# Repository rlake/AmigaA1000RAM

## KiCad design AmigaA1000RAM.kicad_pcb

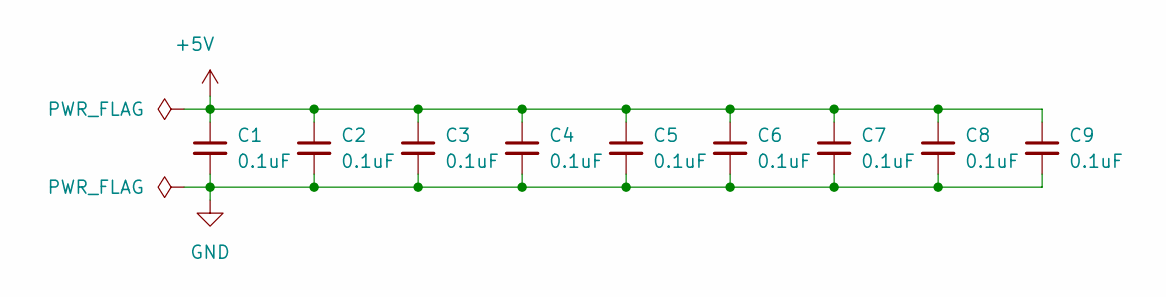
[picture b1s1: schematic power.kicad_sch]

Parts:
C1, C2, C3, C4, C5, C6, C7, C8, C9: 0.1uF; C_0805_2012Metric

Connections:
+5V: C1.1, C2.1, C3.1, C4.1, C5.1, C6.1, C7.1, C8.1, C9.1; also elsewhere on the board
GND: C1.2, C2.2, C3.2, C4.2, C5.2, C6.2, C7.2, C8.2, C9.2; also elsewhere on the board

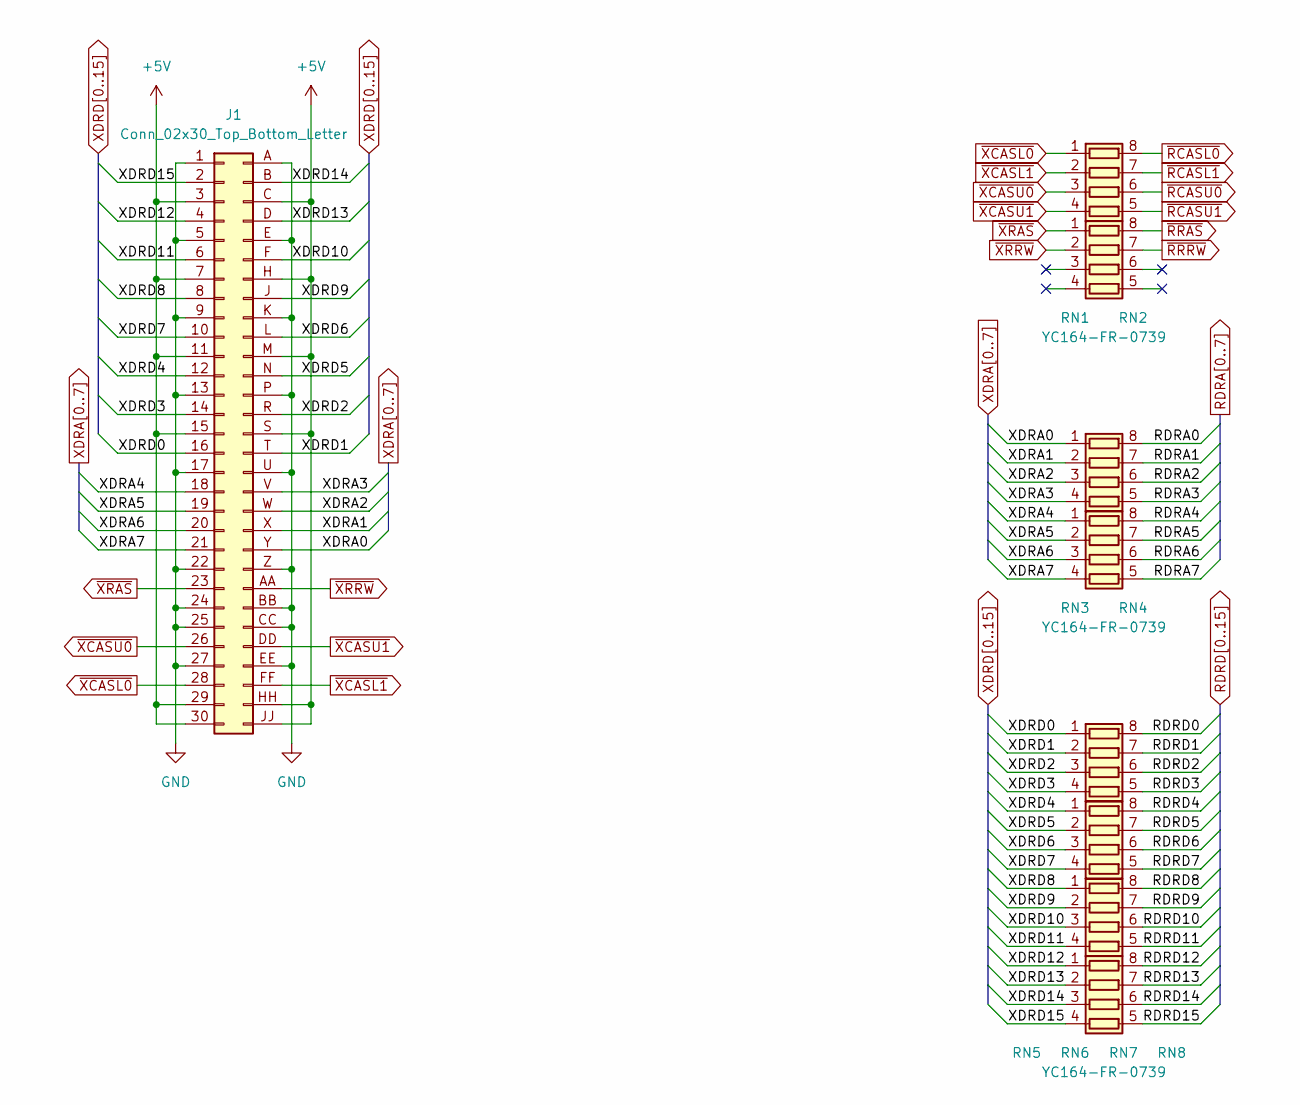
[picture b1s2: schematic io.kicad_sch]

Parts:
J1: Conn_02x30_Top_Bottom_Letter; CardEdgeSocket_2x30_P3.96mm
RN1, RN3, RN6, RN7, RN8: YC164-FR-0768; R_Array_Convex_4x0603
RN2, RN4, RN5: YC164-FR-0739; R_Array_Convex_4x0603

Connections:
+5V: J1.3, J1.7, J1.11, J1.15, J1.29, J1.30, J1.C, J1.H, J1.HH, J1.JJ, J1.M, J1.S; also elsewhere on the board
GND: J1.1, J1.5, J1.9, J1.13, J1.17, J1.22, J1.24, J1.25, J1.27, J1.A, J1.BB, J1.CC, J1.E, J1.EE, J1.K, J1.P, J1.U, J1.Z; also elsewhere on the board
RDRA0: RN3.8 (R1.2); also elsewhere on the board
RDRA1: RN3.7 (R2.2); also elsewhere on the board
RDRA2: RN3.6 (R3.2); also elsewhere on the board
RDRA3: RN3.5 (R4.2); also elsewhere on the board
RDRA4: RN4.8 (R1.2); also elsewhere on the board
RDRA5: RN4.7 (R2.2); also elsewhere on the board
RDRA6: RN4.6 (R3.2); also elsewhere on the board
RDRA7: RN4.5 (R4.2); also elsewhere on the board
RDRD0: RN5.8 (R1.2); also elsewhere on the board
RDRD1: RN5.7 (R2.2); also elsewhere on the board
RDRD2: RN5.6 (R3.2); also elsewhere on the board
RDRD3: RN5.5 (R4.2); also elsewhere on the board
RDRD4: RN6.8 (R1.2); also elsewhere on the board
RDRD5: RN6.7 (R2.2); also elsewhere on the board
RDRD6: RN6.6 (R3.2); also elsewhere on the board
RDRD7: RN6.5 (R4.2); also elsewhere on the board
RDRD8: RN7.8 (R1.2); also elsewhere on the board
RDRD9: RN7.7 (R2.2); also elsewhere on the board
RDRD10: RN7.6 (R3.2); also elsewhere on the board
RDRD11: RN7.5 (R4.2); also elsewhere on the board
RDRD12: RN8.8 (R1.2); also elsewhere on the board
RDRD13: RN8.7 (R2.2); also elsewhere on the board
RDRD14: RN8.6 (R3.2); also elsewhere on the board
RDRD15: RN8.5 (R4.2); also elsewhere on the board
XDRA0: J1.Y, RN3.1 (R1.1)
XDRA1: J1.X, RN3.2 (R2.1)
XDRA2: J1.W, RN3.3 (R3.1)
XDRA3: J1.V, RN3.4 (R4.1)
XDRA4: J1.18, RN4.1 (R1.1)
XDRA5: J1.19, RN4.2 (R2.1)
XDRA6: J1.20, RN4.3 (R3.1)
XDRA7: J1.21, RN4.4 (R4.1)
XDRD0: J1.16, RN5.1 (R1.1)
XDRD1: J1.T, RN5.2 (R2.1)
XDRD2: J1.R, RN5.3 (R3.1)
XDRD3: J1.14, RN5.4 (R4.1)
XDRD4: J1.12, RN6.1 (R1.1)
XDRD5: J1.N, RN6.2 (R2.1)
XDRD6: J1.L, RN6.3 (R3.1)
XDRD7: J1.10, RN6.4 (R4.1)
XDRD8: J1.8, RN7.1 (R1.1)
XDRD9: J1.J, RN7.2 (R2.1)
XDRD10: J1.F, RN7.3 (R3.1)
XDRD11: J1.6, RN7.4 (R4.1)
XDRD12: J1.4, RN8.1 (R1.1)
XDRD13: J1.D, RN8.2 (R2.1)
XDRD14: J1.B, RN8.3 (R3.1)
XDRD15: J1.2, RN8.4 (R4.1)
~RCASL0: RN1.8 (R1.2); also elsewhere on the board
~RCASL1: RN1.7 (R2.2); also elsewhere on the board
~RCASU0: RN1.6 (R3.2); also elsewhere on the board
~RCASU1: RN1.5 (R4.2); also elsewhere on the board
~RRAS: RN2.8 (R1.2); also elsewhere on the board
~RRRW: RN2.7 (R2.2); also elsewhere on the board
~XCASL0: J1.28, RN1.1 (R1.1)
~XCASL1: J1.FF, RN1.2 (R2.1)
~XCASU0: J1.26, RN1.3 (R3.1)
~XCASU1: J1.DD, RN1.4 (R4.1)
~XRAS: J1.23, RN2.1 (R1.1)
~XRRW: J1.AA, RN2.2 (R2.1)

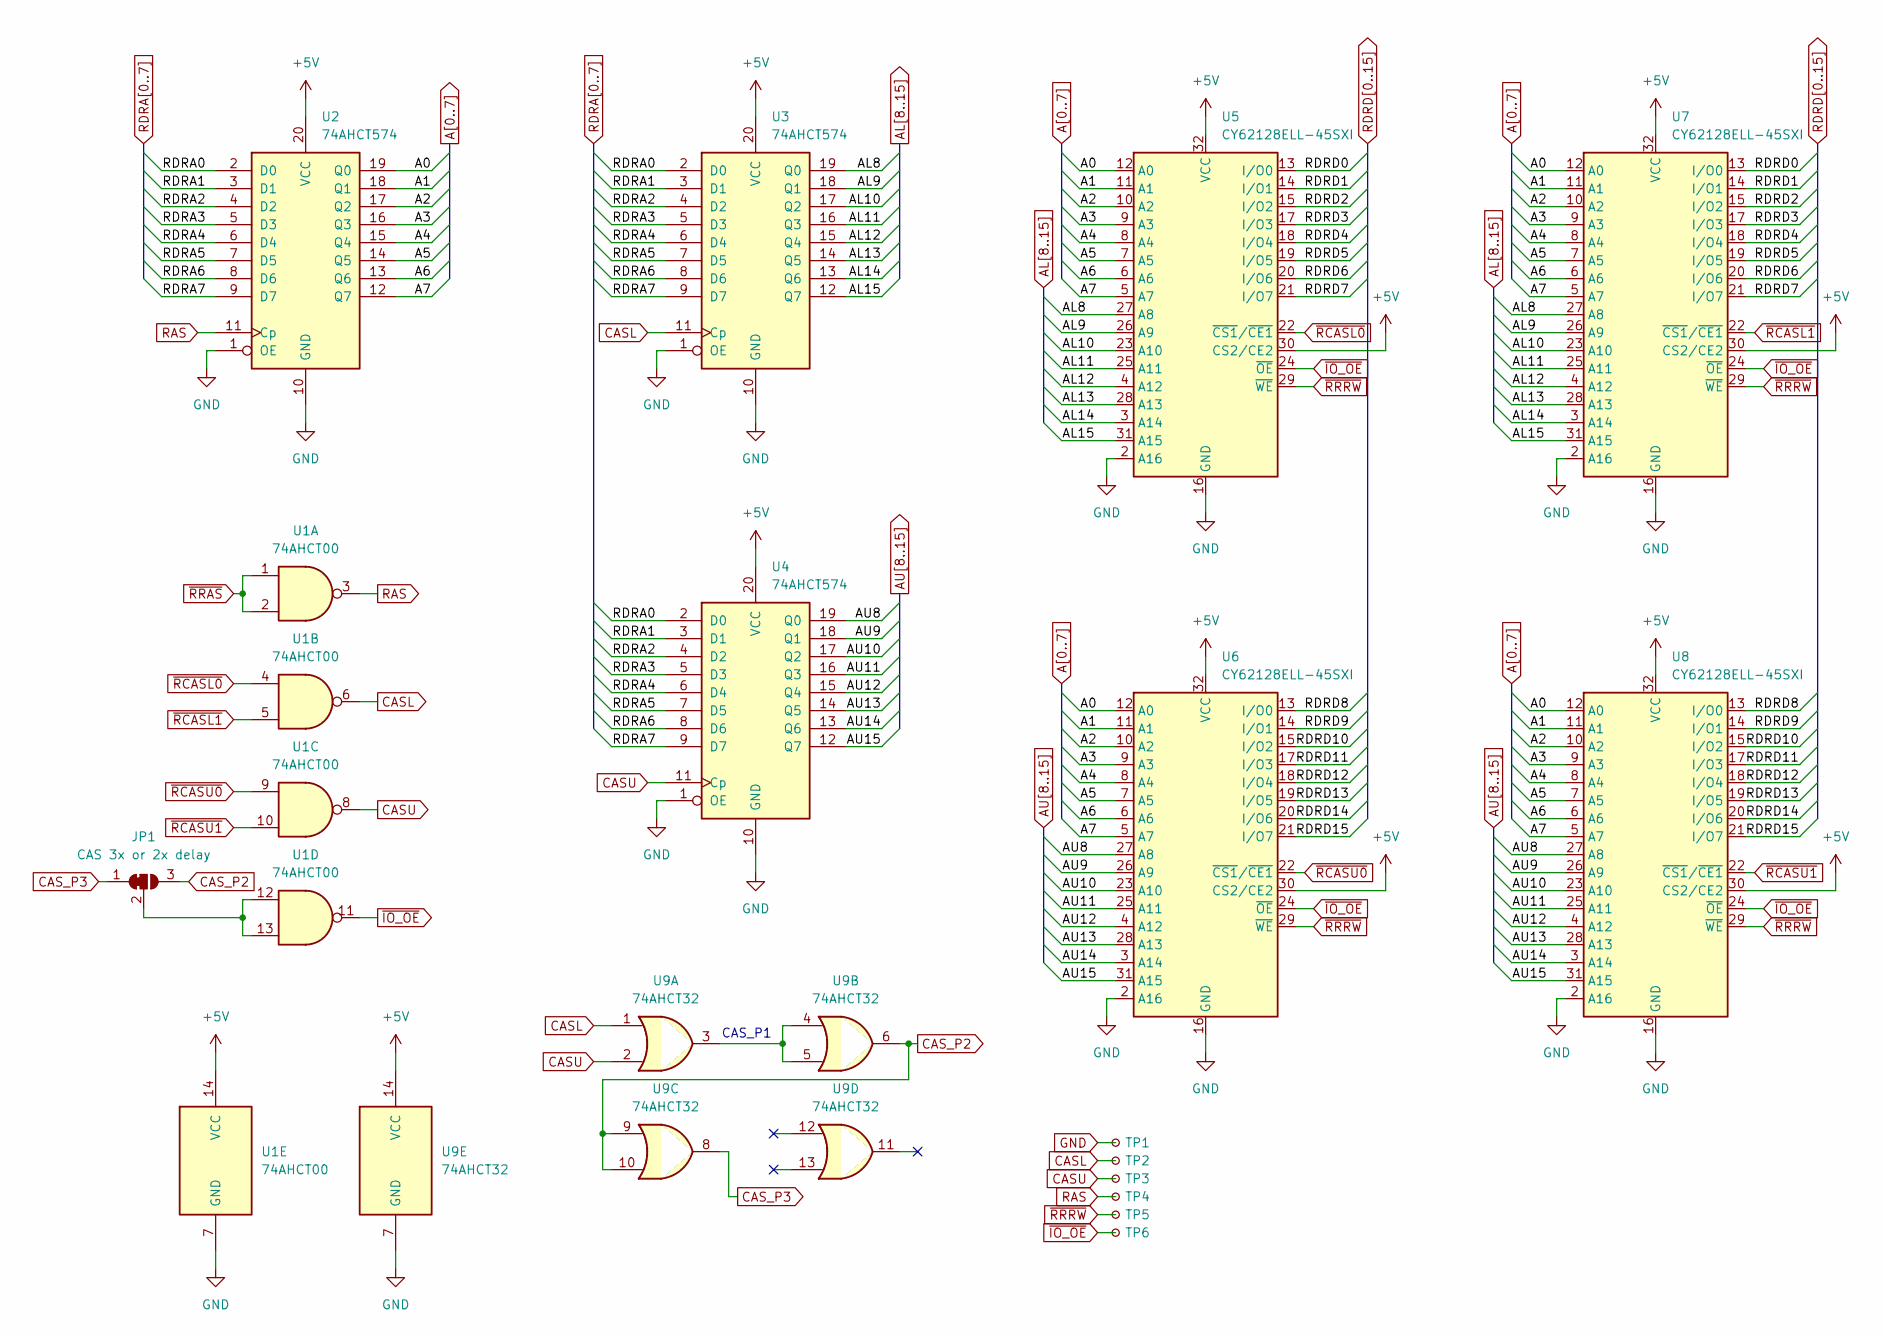
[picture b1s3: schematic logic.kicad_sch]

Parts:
JP1: CAS 3x or 2x delay; SolderJumper-3_P1.3mm_Bridged2Bar12_RoundedPad1.0x1.5mm
TP1: TestPoint_Small; TestPoint_Keystone_5016_Compact
TP2, TP3, TP4, TP5, TP6: TestPoint_Small; TestPoint_Pad_D1.0mm
U1: 74AHCT00; SOIC-14_3.9x8.7mm_P1.27mm
U2, U3, U4: 74AHCT574; SOIC-20W_7.5x12.8mm_P1.27mm
U5, U6, U7, U8: CY62128ELL-45SXI; SOP-32_11.305x20.495mm_P1.27mm
U9: 74AHCT32; SOIC-14_3.9x8.7mm_P1.27mm

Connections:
+5V: U1.14 (VCC), U2.20 (VCC), U3.20 (VCC), U4.20 (VCC), U5.30 (CS2/CE2), U5.32 (VCC), U6.30 (CS2/CE2), U6.32 (VCC), U7.30 (CS2/CE2), U7.32 (VCC), U8.30 (CS2/CE2), U8.32 (VCC), U9.14 (VCC); also elsewhere on the board
A0: U2.19 (Q0), U5.12 (A0), U6.12 (A0), U7.12 (A0), U8.12 (A0)
A1: U2.18 (Q1), U5.11 (A1), U6.11 (A1), U7.11 (A1), U8.11 (A1)
A2: U2.17 (Q2), U5.10 (A2), U6.10 (A2), U7.10 (A2), U8.10 (A2)
A3: U2.16 (Q3), U5.9 (A3), U6.9 (A3), U7.9 (A3), U8.9 (A3)
A4: U2.15 (Q4), U5.8 (A4), U6.8 (A4), U7.8 (A4), U8.8 (A4)
A5: U2.14 (Q5), U5.7 (A5), U6.7 (A5), U7.7 (A5), U8.7 (A5)
A6: U2.13 (Q6), U5.6 (A6), U6.6 (A6), U7.6 (A6), U8.6 (A6)
A7: U2.12 (Q7), U5.5 (A7), U6.5 (A7), U7.5 (A7), U8.5 (A7)
AL8: U3.19 (Q0), U5.27 (A8), U7.27 (A8)
AL9: U3.18 (Q1), U5.26 (A9), U7.26 (A9)
AL10: U3.17 (Q2), U5.23 (A10), U7.23 (A10)
AL11: U3.16 (Q3), U5.25 (A11), U7.25 (A11)
AL12: U3.15 (Q4), U5.4 (A12), U7.4 (A12)
AL13: U3.14 (Q5), U5.28 (A13), U7.28 (A13)
AL14: U3.13 (Q6), U5.3 (A14), U7.3 (A14)
AL15: U3.12 (Q7), U5.31 (A15), U7.31 (A15)
AU8: U4.19 (Q0), U6.27 (A8), U8.27 (A8)
AU9: U4.18 (Q1), U6.26 (A9), U8.26 (A9)
AU10: U4.17 (Q2), U6.23 (A10), U8.23 (A10)
AU11: U4.16 (Q3), U6.25 (A11), U8.25 (A11)
AU12: U4.15 (Q4), U6.4 (A12), U8.4 (A12)
AU13: U4.14 (Q5), U6.28 (A13), U8.28 (A13)
AU14: U4.13 (Q6), U6.3 (A14), U8.3 (A14)
AU15: U4.12 (Q7), U6.31 (A15), U8.31 (A15)
CASL: TP2.1 (1_1), U1.6, U3.11 (Cp), U9.1
CASU: TP3.1 (1_1), U1.8, U4.11 (Cp), U9.2
CAS_P2: JP1.3 (B), U9.6, U9.9, U9.10
CAS_P3: JP1.1 (A), U9.8
GND: TP1.1 (1_1), U1.7 (GND), U2.1 (OE), U2.10 (GND), U3.1 (OE), U3.10 (GND), U4.1 (OE), U4.10 (GND), U5.2 (A16), U5.16 (GND), U6.2 (A16), U6.16 (GND), U7.2 (A16), U7.16 (GND), U8.2 (A16), U8.16 (GND), U9.7 (GND); also elsewhere on the board
unnamed: JP1.2 (C), U1.12, U1.13
unnamed: U9.3, U9.4, U9.5
RAS: TP4.1 (1_1), U1.3, U2.11 (Cp)
RDRA0: U2.2 (D0), U3.2 (D0), U4.2 (D0); also elsewhere on the board
RDRA1: U2.3 (D1), U3.3 (D1), U4.3 (D1); also elsewhere on the board
RDRA2: U2.4 (D2), U3.4 (D2), U4.4 (D2); also elsewhere on the board
RDRA3: U2.5 (D3), U3.5 (D3), U4.5 (D3); also elsewhere on the board
RDRA4: U2.6 (D4), U3.6 (D4), U4.6 (D4); also elsewhere on the board
RDRA5: U2.7 (D5), U3.7 (D5), U4.7 (D5); also elsewhere on the board
RDRA6: U2.8 (D6), U3.8 (D6), U4.8 (D6); also elsewhere on the board
RDRA7: U2.9 (D7), U3.9 (D7), U4.9 (D7); also elsewhere on the board
RDRD0: U5.13 (I/O0), U7.13 (I/O0); also elsewhere on the board
RDRD1: U5.14 (I/O1), U7.14 (I/O1); also elsewhere on the board
RDRD2: U5.15 (I/O2), U7.15 (I/O2); also elsewhere on the board
RDRD3: U5.17 (I/O3), U7.17 (I/O3); also elsewhere on the board
RDRD4: U5.18 (I/O4), U7.18 (I/O4); also elsewhere on the board
RDRD5: U5.19 (I/O5), U7.19 (I/O5); also elsewhere on the board
RDRD6: U5.20 (I/O6), U7.20 (I/O6); also elsewhere on the board
RDRD7: U5.21 (I/O7), U7.21 (I/O7); also elsewhere on the board
RDRD8: U6.13 (I/O0), U8.13 (I/O0); also elsewhere on the board
RDRD9: U6.14 (I/O1), U8.14 (I/O1); also elsewhere on the board
RDRD10: U6.15 (I/O2), U8.15 (I/O2); also elsewhere on the board
RDRD11: U6.17 (I/O3), U8.17 (I/O3); also elsewhere on the board
RDRD12: U6.18 (I/O4), U8.18 (I/O4); also elsewhere on the board
RDRD13: U6.19 (I/O5), U8.19 (I/O5); also elsewhere on the board
RDRD14: U6.20 (I/O6), U8.20 (I/O6); also elsewhere on the board
RDRD15: U6.21 (I/O7), U8.21 (I/O7); also elsewhere on the board
~IO_OE: TP6.1 (1_1), U1.11, U5.24 (~OE), U6.24 (~OE), U7.24 (~OE), U8.24 (~OE)
~RCASL0: U1.4, U5.22 (~CS1/~CE1); also elsewhere on the board
~RCASL1: U1.5, U7.22 (~CS1/~CE1); also elsewhere on the board
~RCASU0: U1.9, U6.22 (~CS1/~CE1); also elsewhere on the board
~RCASU1: U1.10, U8.22 (~CS1/~CE1); also elsewhere on the board
~RRAS: U1.1, U1.2; also elsewhere on the board
~RRRW: TP5.1 (1_1), U5.29 (~WE), U6.29 (~WE), U7.29 (~WE), U8.29 (~WE); also elsewhere on the board

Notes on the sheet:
CAS_P1

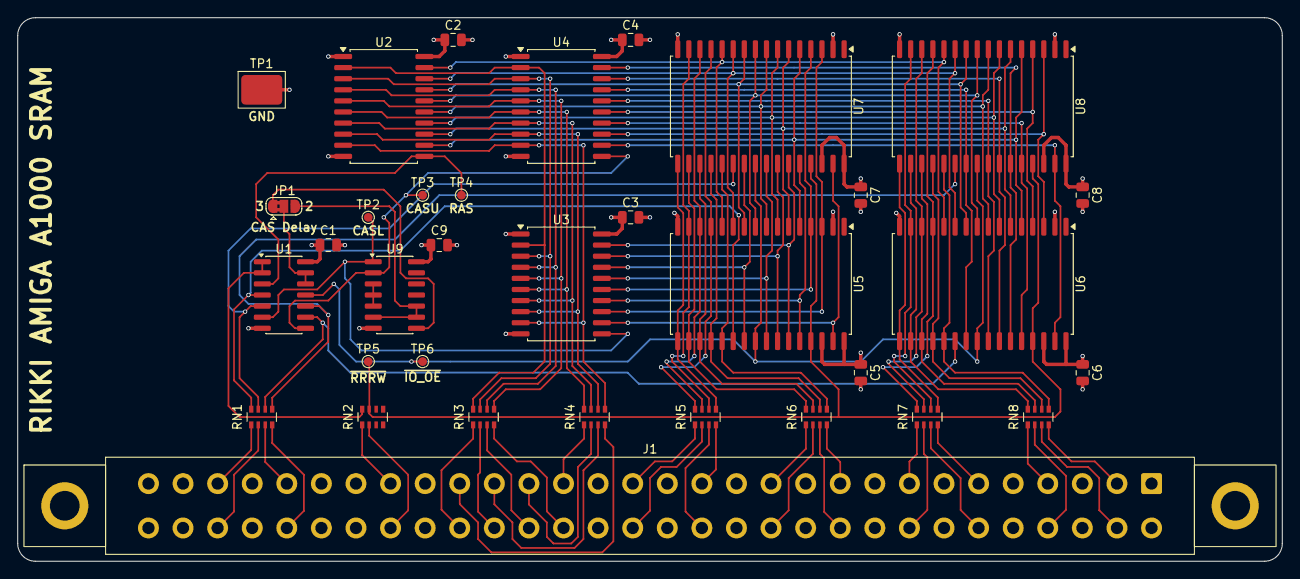
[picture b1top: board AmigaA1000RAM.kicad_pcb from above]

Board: 4 copper layers, 144.8 x 62.2 mm, 34 parts (0 on the bottom side), 94 nets.

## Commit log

2026-04-27 Initial KiCad project
2026-04-27 Add symbol library
2026-05-16 Add footprints for resistor array, test
2026-05-16 Amiga A1000 RAM Schematic
2026-05-16 Amiga A1000 RAM PCB
2026-05-16 Amiga A1000 RAM BOM
2026-05-16 Amiga A1000 RAM PCB Render
2026-05-19 Add symbol for card edge connector
2026-05-19 Add footprint for card edge connector
2026-05-20 PCB updates for Aisler
2026-05-20 Update Schematic for card edge connector
2026-05-23 Update PCB for card edge connector
